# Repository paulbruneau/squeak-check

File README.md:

# Squeak Check!

A bench tester for Midway's Cheap Squeak Deluxe, Sounds Good and Turbo Cheap Squeak arcade sound boards (Spy Hunter, Rampage, Xenophobe, Sarge and more). Power a sound board on the bench, dial a sound 0–F, press PLAY, and hear it on line out, with no game CPU board, harness or cabinet.

By Ethical Paul.

**Website:** the full write-up (how the boards work, pinouts, hook-up diagram, history) is in `index.html`, published with GitHub Pages.

## Files

| Path | What it is |
| --- | --- |
| `fab/SqueakCheck_RevE6_Gerbers.zip` | Gerbers and drill files, Rev E.6 (98 × 80 mm, 2 layers, 1.6 mm) |
| `fab/Schematic_RevE6.pdf` | Schematic, drawn from and checked against the board netlist |
| `fab/KiCad/` | KiCad 8 schematic and PCB, generated from the board data (refill the zone and run DRC after opening) |
| `fab/BOM.csv` | Bill of materials with Mouser part numbers |
| `fab/Harness_Pin_Map.csv` | Every harness hole: connector, pin, label, net, position |
| `fab/README.txt` | Revision history and verification notes |
| `reference/Cheap_Squeak_Deluxe_Schematic.pdf` | Midway's Cheap Squeak Deluxe schematic (A080-91671), for reference |
| `tools/` | Scripts used to edit and check the Gerbers (see `tools/README.md`) |
| `squeak-tap/` | **Squeak Tap**, a companion project: plugs into the CSD's DAC socket and records the sound board's audio as the exact digital values, straight to WAV (see `squeak-tap/README.md`) |
| `fab/fonts/` | Barlow Condensed SemiBold, the silkscreen credit font (SIL OFL) |
| `index.html`, `images/` | The website |

## Building

Fit the hex dial (SW1) with the 0 on its dial toward the top of the board, next to the "0" on the silkscreen. It fits either way round, and the wrong way swaps the sound bits. On Rev E.5 boards the 0 goes toward the bottom edge.

## Ordering boards

Upload the Gerber zip to any 2-layer PCB fab: FR-4, 1.6 mm, 1 oz copper, any mask colour, white silk, HASL or ENIG.

## Squeak Tap

`squeak-tap/` holds a second, separate project: a DAC-socket adapter and a Raspberry Pi Pico capture board, ordered together on one panel and snapped apart. It records the 10-bit values the Cheap Squeak Deluxe writes to its AD7533 DAC and turns them into WAV files, for a bit-exact copy of a sound such as the Spy Hunter theme. Gerbers, schematic, BOM, firmware and the PC tool are all in that folder. Rev A has not been built yet.

## Rights

© 2026 Ethical Paul. All rights reserved. No license is granted yet; ask before reusing the files.

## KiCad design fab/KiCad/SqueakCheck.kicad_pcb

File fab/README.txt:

SQUEAK CHECK! — Midway sound board bench tester — REV E.6
By Ethical Paul
=========================================================

WHAT IT TESTS
-------------
Verified against the original Bally/Midway schematics (Spy Hunter, Rampage/Star
Guards and Sarge manuals). All three boards share the same J1/J2/J3 pinout and the
same command interface (4 sound-select bits + SIRQ strobe, 2 status bits back):

  Cheap Squeak Deluxe  A080-91671 (68000)   Spy Hunter, Turbo Tag (proto)
  Sounds Good          A080-91671-G000 PCB  Rampage, Power Drive, Star Guards,
                       (a later revision of  Xenophobe, Spy Hunter II, Blasted,
                        the same bare board) Intl. Team Laser (proto)
  Turbo Cheap Squeak   (6809)               Sarge, Max RPM, Demolition Derby,
                                            Spy Hunter II (2nd board)

NOT compatible: Super Sound I/O (SSIO), and the Williams System 11 boards in
Arch Rivals / Pigskin / Tri-Sports. Pinball-era Bally boards (Cheap Squeak,
Sounds Deluxe, pinball TCS) use different harnesses and were not checked.

REV E.6: HEX DIAL FITS WITH ITS 0 AT THE TOP.
- On E.5 the SW1 footprint's pin map assumed the Grayhill 94HBB16T went in with
  the 0 on its dial toward the BOTTOM of the board. The switch fits its holes
  either way round, and fitted with 0 at the top (the natural way) it swapped
  SOUND0<->SOUND1 and SOUND2<->SOUND3 (dial 1 sent 2, dial 4 sent 8, etc.).
- E.6 turns the footprint's pin numbers 180 degrees: with the 0 at the top,
  pin 1 is the top-left hole and drives SOUND0. Hole positions are unchanged;
  the four sound tracks are swapped where they meet the resistors:
    SW1 top-left hole     -> S0 (R5/R6)   front copper
    SW1 bottom-right hole -> S1 (R3/R4)   back copper
    SW1 bottom-left hole  -> S2 (R9/R10)   front copper
    SW1 top-right hole    -> S3 (R7/R8)   back copper
- Silkscreen: a "0" replaces the top dial tick and an "8" the bottom one, so
  the switch's printed 0 lines up with the silk 0. REV E.5 -> REV E.6.
- Silkscreen text: every label is now at least 1.1 mm tall (capital height)
  with strokes of about 0.2 mm; the smallest used to be 0.72 mm. Grown in
  place: the LED legend, LINE LEVEL note, power-tag pills, F1/F2/5V/12V,
  resistor values, column headings, TRIGGER, 1uF, AWG notes, LOUDER/VOLUME,
  PICK A SOUND, INSERT POWER / KK-396, and the size and mounting notes.
  "5V 1A · 12V 0.5A" is now two lines ("5V 1A" / "12V 0.5A") to clear the
  RCA jack outline. Nothing moved onto pads; copper and drills unchanged.
- Header under the title is now two stacks. Left: "By Ethical Paul" (1.75 mm)
  over "paul@ethicalpaul.com" (1.47 mm), both Barlow Condensed SemiBold. Right, at 1.3 mm: CHEAP SQUEAK DELUXE / SOUNDS GOOD
  / TURBO CHEAP SQUEAK (replaces the one-line "... · BENCH TESTER" subtitle).
- REV E.6 / board size / mounting block scaled up 1.6x (REV 2.2 mm, notes
  1.8 mm) and centred in the open area between the SOUND2 row and J2.
- Three small ground-pour keep-outs on the back (around 29.8,51.8 / 32.3,47.4 /
  30.9,30.1 in Gerber coordinates) stop the rerouted tracks from leaving an
  unconnected pour island and two thin necks.
- Schematic unchanged electrically (dial 1-2-4-8 -> SOUND0-3); the KiCad
  symbol now lists SW1's pins in footprint order (1, CL, 4, 8, CR, 2).
- E.5 BOARDS: fit SW1 with its 0 toward the BOTTOM edge to get the right bits.
- Resistor references renumbered to the usual R1-R13 (silkscreen unchanged;
  it prints values, not references). Old -> new: RSIRQ R1, RIRQ R2, RS1 R3,
  RPD1 R4, RS0 R5, RPD0 R6, RS3 R7, RPD3 R8, RS2 R9, RPD2 R10, RL1 R11,
  RL2 R12, RRST R13. The notes below use the new names.
Every other hole, part, net and label is unchanged from E.5.

REV E.5: POWER PROTECTION AND INDICATORS (review feedback).
- F1 (Bourns MF-R135, 1.35 A hold) on +5 V and F2 (MF-R050, 0.5 A hold) on +12 V:
  resettable fuses right after the power header, so a shorted sound board
  can't cook the tester's traces or connector.
- D1/D2 green LEDs on +5 V and +12 V, AFTER the fuses (1k / 3.3k, ~3 mA): a dark
  LED means no supply or a tripped fuse.
- Suggested supply printed on the board: 5 V 1 A, 12 V 0.5 A (estimated from
  the sound board's chips; measure your own board).
- Mounting note on the silk: M3 or #4-40, pan head no bigger than 5.6 mm.
- LED self-test legend moved into the how-to panel to make room.
Harness holes, pin order, names and every sound-board signal are unchanged.

REV E.4: BOARD NARROWED 108 -> 98 MM. J1 stays on the left edge; the resistor
block tucked in against the J1 labels and everything else slid left (J2, J3, pot,
RCA jacks and power header move as groups, with pitches, hole sizes, pin order and
labels all unchanged). +12V now runs between the SOUND2 trace (SOUND3 from
E.6 on) and the RESET button on the back. Netlist identical to E.3.

REV E.3: VOLUME POT ON THE BOARD. The J5 A/W/B wire pads are gone; RV1 (Bourns
PTV09A-4020U-B102, 1k linear, 9 mm, vertical 20 mm knurled shaft
you turn by hand - no knob needed) sits in the
bottom-right corner, wired pin 1 = VOL_END_B (J3-12), pin 2 = VOL_WIPER (J3-1),
pin 3 = VOL_END_A (J3-10) so turning it CLOCKWISE = LOUDER (the MC3340 attenuates
more as the wiper voltage rises). Its two side tabs are soldered to ground for
strength. Every other net, hole and label is unchanged from E.2. Part numbers in
BOM.csv are Mouser numbers.

REV E.2 (layout): PLAY button and its debounce cap moved right beside the hex
dial; "By Ethical Paul" added under the title. No circuit change from E.1.

REV E.1 CHANGES (from Rev E / Rev D5)
------------------------------------
1. RESET POLARITY FIXED. J2-9/10 is active-LOW on all three boards (e.g. CSD:
   100k pull-up -> 40106 -> 74LS04 -> diodes pull the 68000 RST/HALT low). Rev D5
   held RESET low through 10k, which would keep the board in reset permanently.
   Now: R13 (10k) pulls RESET up to +5V; the RESET button pulls it to GND.
2. SIRQ polarity hardwired "fire low"; JP1 removed. All three boards idle SIRQ
   high (100k on-board pull-up) and the same game hardware drives them with the
   same signal (Spy Hunter II feeds a Sounds Good and a TCS from the same control
   bits). R2 (10k) pulls SIRQ up to +5V; PLAY pulls it to GND.
3. PLAY debounce: C1 1 uF across the button (~10 ms with R2).
4. E-GND (J2-7) tied to GND. Sounds Good grounds it on-board; CSD/TCS use it as
   the return for their input filter capacitors.
Harness hole sizes, pin order, duplicate pins and all silk names are unchanged.

USING IT
--------
Power-up: the sound board's green LED flashes once per passed self-test:
  1-4 = ROMs (U7, U8, U17, U18), 5 = RAM (U6, U16), 6 = PIA (U9).
  Six flashes = pass. Where it stops = the failed step. (Star Guards manual.)

Red TEST button ON the sound board: wired to the 68000's interrupt lines
(pulls IPL0-2 -> level 7). What it does is decided by that game's ROMs. On the
sister pinball boards it plays one fixed test sound (a "bong" or an explosion)
or just reboots the board; it is not a cycle through all sounds.

Sound numbers: the connector carries 4 bits per strobe; one dial+PLAY press
sends the number on the dial. The command list lives in each game's sound ROMs
and is not documented in MAME. Spy Hunter CSD (only the two low bits matter):
1 = full Peter Gunn theme, 2 = short intro, 3 = the "player died" ending (send
it while the theme is playing). Other games' ROMs may expect a sequence of
presses.

Start with the VOLUME knob turned down (fully counter-clockwise). Line-level mono audio
appears on both RCA jacks; feed an amplifier or powered speaker.

VERIFICATION (Rev E.6)
---------------------
Gerbers re-read with an independent parser and rasterised at 0.04 mm:
- Netlist: every one of the 135 holes' copper checked against the intended
  net (23 nets): 0 shorts, 0 opens, 0 unconnected copper islands.
- Clearance between different nets: 0.50 mm minimum on top, 0.40 mm on the
  back (rule 0.30 mm). Same as E.5; the rerouted tracks have 0.68 mm or more.
- Thin copper: the new keep-outs leave four tiny pointed tips of ground pour
  (under 0.3 mm long), the same kind of feature E.5 already had at its
  thermal spokes and corners. Fabs handle these.
- Drills: 98 plated + 37 non-plated, all on their pads; files unchanged from E.5.
- Silkscreen: none on exposed pads; all text at least 1.1 mm tall and
  0.2 mm or more from other silk (the power tags keep their E.5 spacing).
- KiCad PCB tracks and pads redrawn and compared with the Gerber copper:
  identical on top, and every KiCad track present on the back.
(No KiCad/Altium DRC was run here. Preview the zip in your fab's Gerber viewer
before ordering.)

ORDERING
--------
2 layers, FR-4, 1.6 mm, 1 oz, any mask colour, white silk, ENIG or HASL.
98 x 80 mm. Upload SqueakCheck_RevE6_Gerbers.zip as it is.

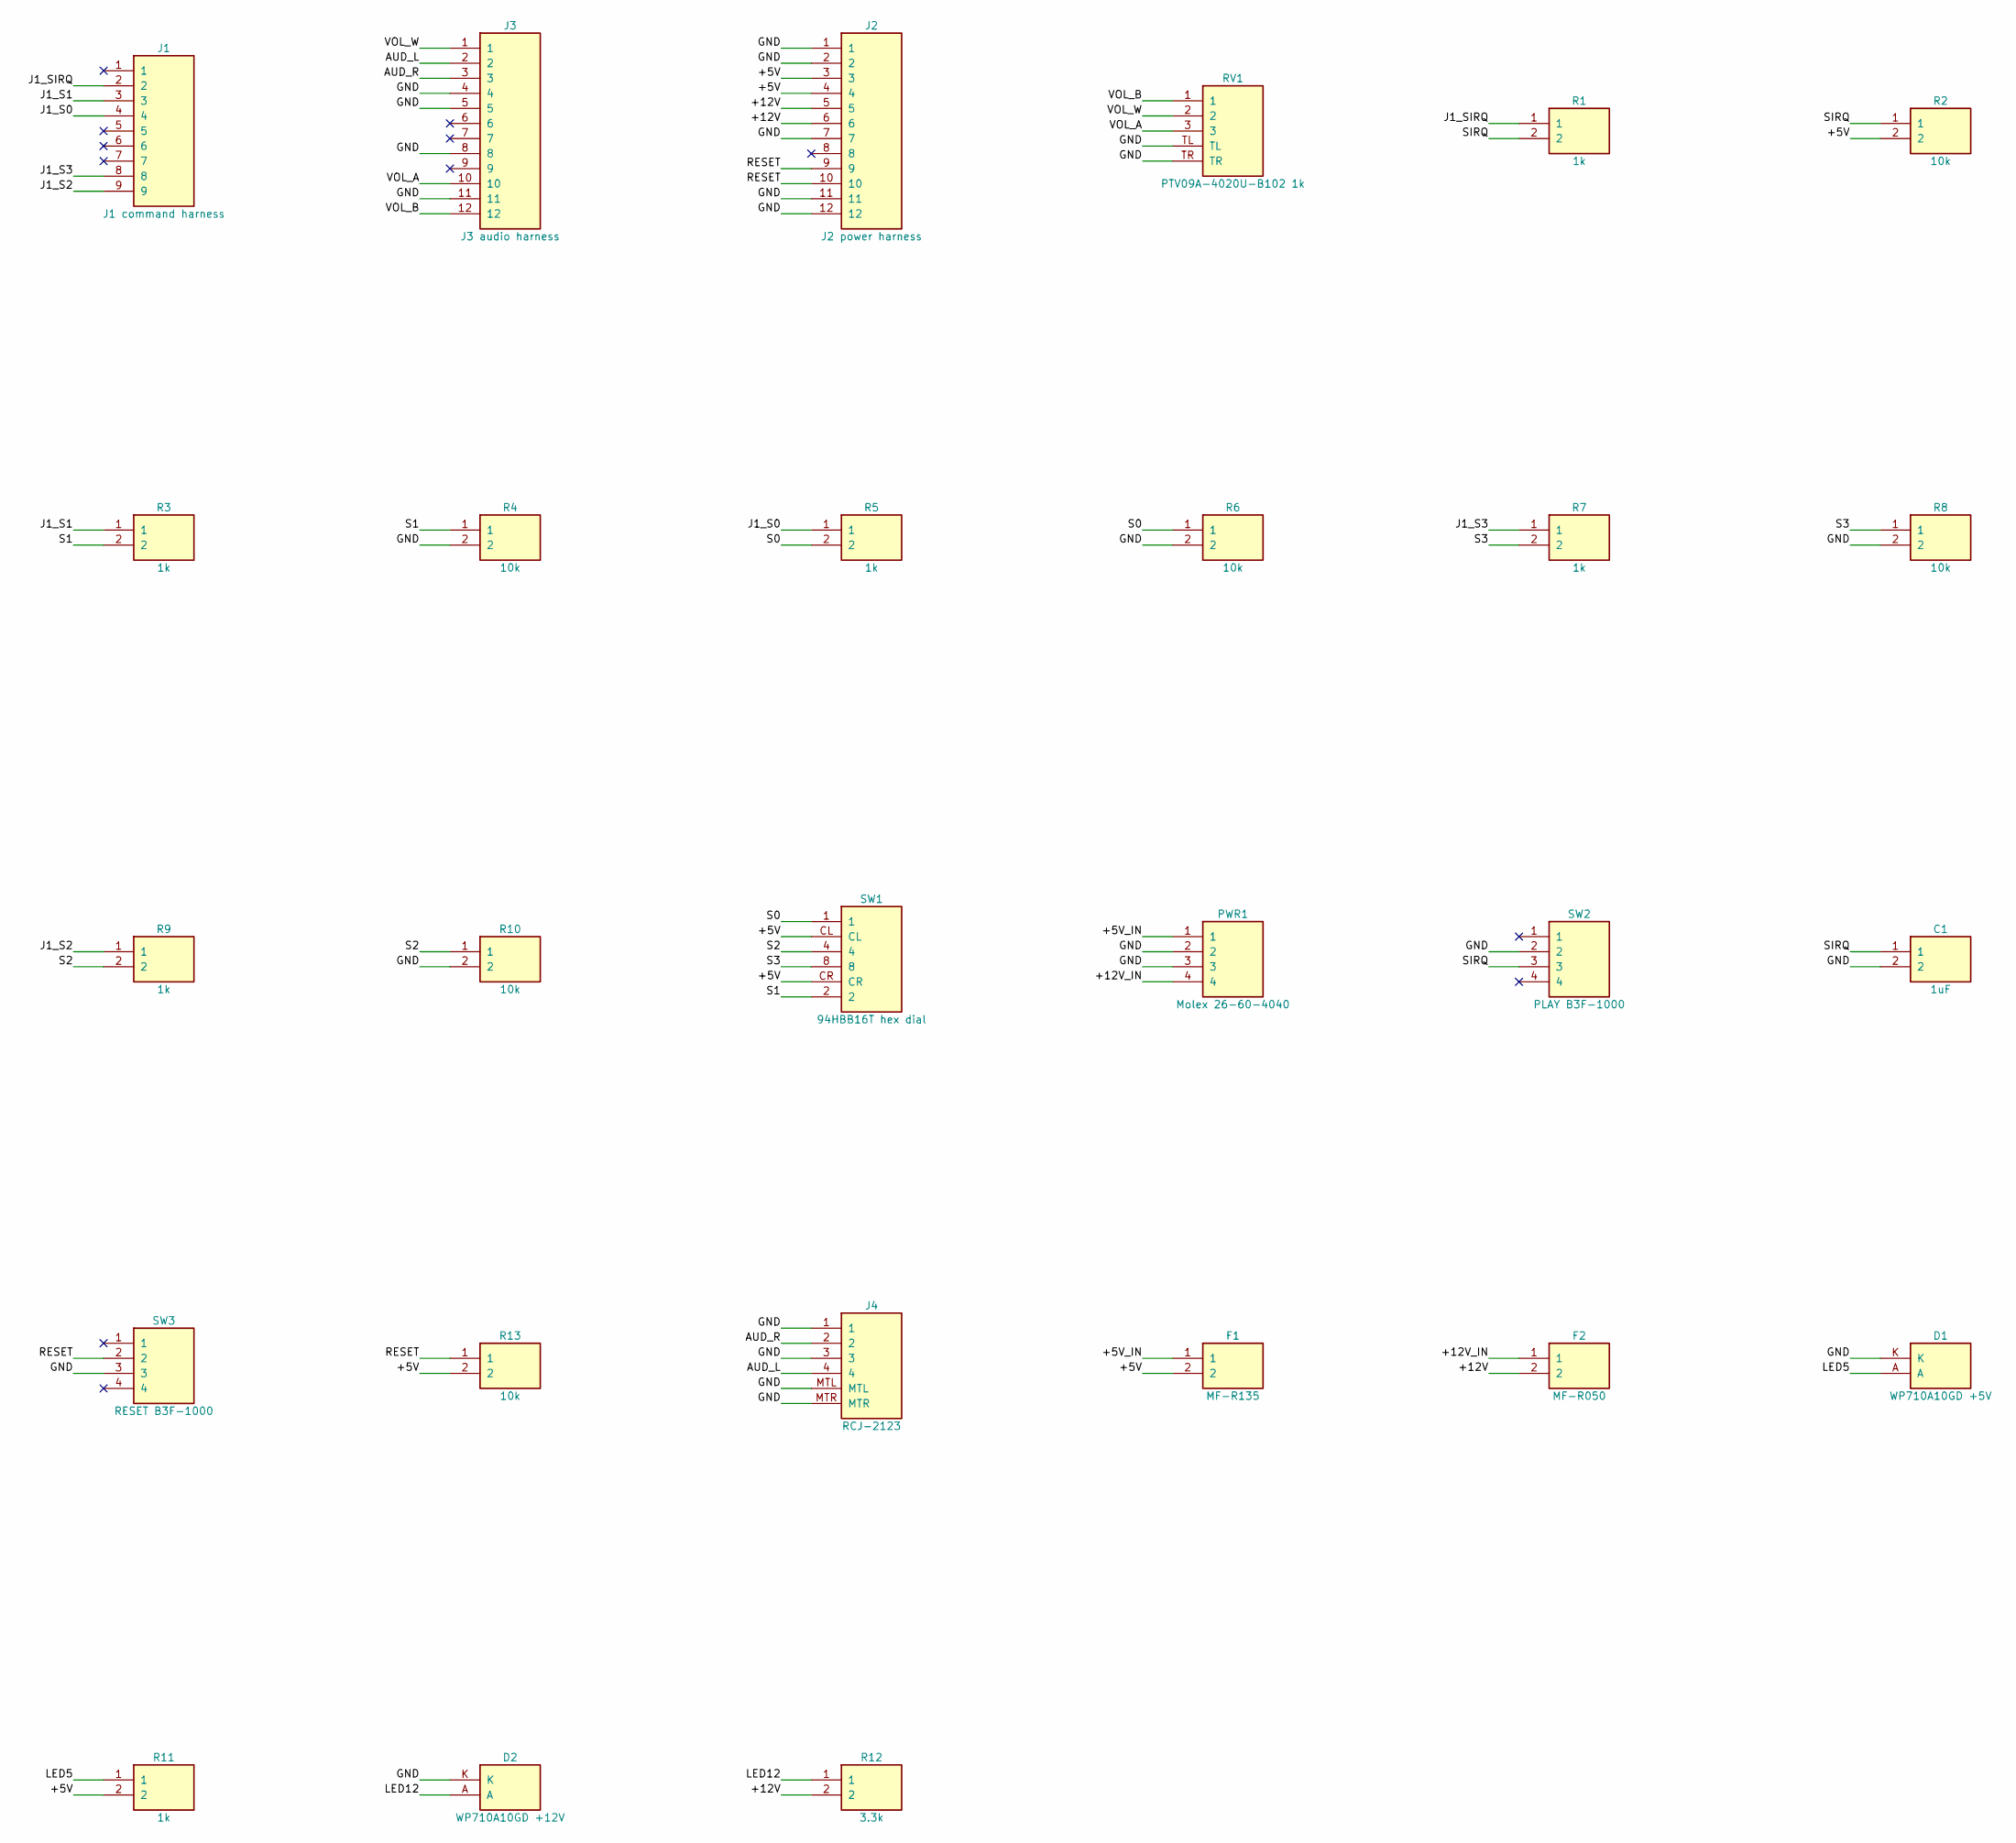
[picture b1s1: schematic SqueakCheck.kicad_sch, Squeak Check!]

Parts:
C1: 1uF; C1
D1: WP710A10GD +5V; D1
D2: WP710A10GD +12V; D2
F1: MF-R135; F1
F2: MF-R050; F2
J1: J1 command harness; J1
J2: J2 power harness; J2
J3: J3 audio harness; J3
J4: RCJ-2123; J4
PWR1: Molex 26-60-4040; PWR1
R1: 1k; R1
R2: 10k; R2
R3: 1k; R3
R4: 10k; R4
R5: 1k; R5
R6: 10k; R6
R7: 1k; R7
R8: 10k; R8
R9: 1k; R9
R10: 10k; R10
R11: 1k; R11
R12: 3.3k; R12
R13: 10k; R13
RV1: PTV09A-4020U-B102 1k; RV1
SW1: 94HBB16T hex dial; SW1
SW2: PLAY B3F-1000; SW2
SW3: RESET B3F-1000; SW3

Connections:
+5V: F1.2, J2.3, J2.4, R2.2, R11.2, R13.2, SW1.CL, SW1.CR
+5V_IN: F1.1, PWR1.1
+12V: F2.2, J2.5, J2.6, R12.2
+12V_IN: F2.1, PWR1.4
AUD_L: J3.2, J4.4
AUD_R: J3.3, J4.2
GND: C1.2, D1.K, D2.K, J2.1, J2.2, J2.7, J2.11, J2.12, J3.4, J3.5, J3.8, J3.11, J4.1, J4.3, J4.MTL, J4.MTR, PWR1.2, PWR1.3, R4.2, R6.2, R8.2, R10.2, RV1.TL, RV1.TR, SW2.2, SW3.3
J1_S0: J1.4, R5.1
J1_S1: J1.3, R3.1
J1_S2: J1.9, R9.1
J1_S3: J1.8, R7.1
J1_SIRQ: J1.2, R1.1
LED5: D1.A, R11.1
LED12: D2.A, R12.1
RESET: J2.9, J2.10, R13.1, SW3.2
S0: R5.2, R6.1, SW1.1
S1: R3.2, R4.1, SW1.2
S2: R9.2, R10.1, SW1.4
S3: R7.2, R8.1, SW1.8
SIRQ: C1.1, R1.2, R2.1, SW2.3
VOL_A: J3.10, RV1.3
VOL_B: J3.12, RV1.1
VOL_W: J3.1, RV1.2

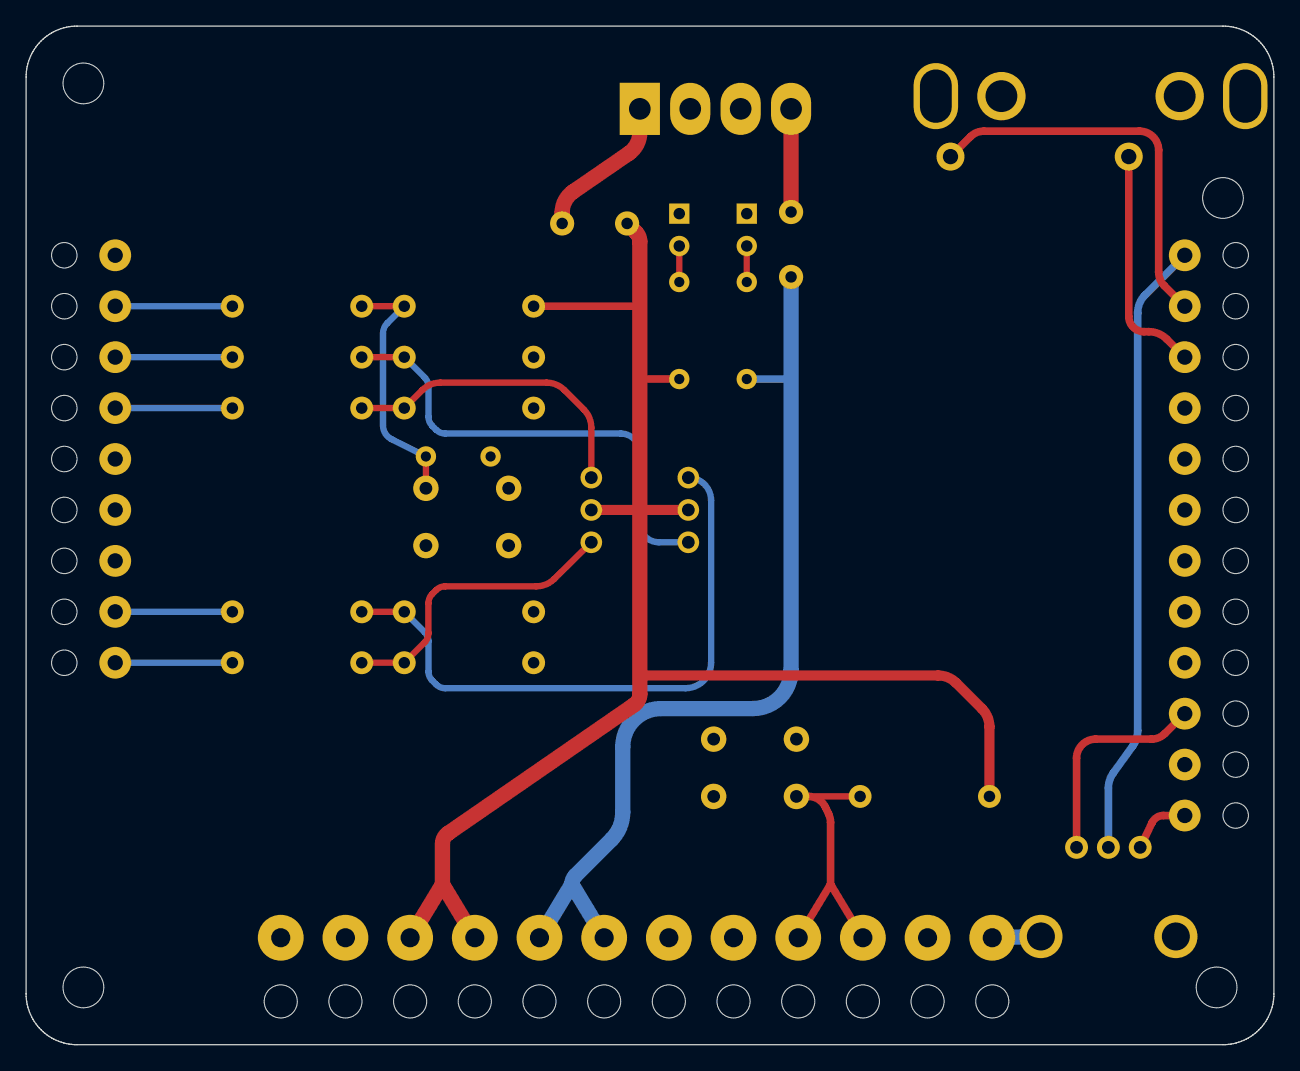
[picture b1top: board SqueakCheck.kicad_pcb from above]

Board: 2 copper layers, 98.0 x 80.0 mm, 64 parts (0 on the bottom side), 23 nets.

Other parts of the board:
H1, H2, H3, H4, H5, H6, H7, H8, H9, H10, H11, H12, H13, H14, H15, H16, H17, H18, H19, H20, H21: hole 2; NPTH_2mm
H22, H23, H24, H25, H26, H27, H28, H29, H30, H31, H32, H33: hole 2.6; NPTH_2.6mm
H34, H35, H36, H37: hole 3.2; NPTH_3.2mm

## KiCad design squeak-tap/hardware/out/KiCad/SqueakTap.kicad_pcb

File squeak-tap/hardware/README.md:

# Squeak Tap Rev A: board files

Two boards on one 91 × 60 mm panel, separated by a 2 mm routed gap and held by three mouse-bite tabs laid out to JLCPCB's mouse-bite guide. Order the panel, snap the tabs, sand the nubs. By Ethical Paul.

| Board | Size | What it does |
| --- | --- | --- |
| 1, DAC adapter | 34 × 37 mm | Plugs into the CSD's DAC socket (U10). The original AD7533 sits in X1, 12.7 mm to the side, and still drives the CSD's audio. The 10 data bits and ground go to J2. |
| 2, capture board | 55 × 60 mm | Two 74LVC245 buffers (5 V in, 3.3 V out), a 100 k pull-down network and a Pico 2 that samples the bits at 960 kHz and streams them over USB. MARK button on GP12. |

## Files

| Path | What it is |
| --- | --- |
| `out/SqueakTap_RevA_Gerbers.zip` | Gerbers + Excellon (PTH and NPTH), the file to upload |
| `out/Schematic_RevA.pdf` | Schematic, two A3 sheets, drawn from the board netlist |
| `out/BOM.csv` | Bill of materials |
| `out/Ribbon_Pin_Map.csv` | Every ribbon pin: signal, CSD source, buffer input, Pico GPIO |
| `out/KiCad/SqueakTap.kicad_pcb` | KiCad 8 PCB: copper, drills, outline, nets, GND zone (refill it after opening; silkscreen lives in the Gerbers) |
| `make_panel.py` | Generates the Gerbers, drills and KiCad file |
| `make_docs.py` | Generates the schematic, BOM and pin map from the KiCad netlist |
| `tools/` | Squeak Check's Gerber reader, DRC and renderer, set for this panel |

Regenerate with `python3 make_panel.py && python3 make_docs.py`, then check with `python3 tools/drc.py out/Gerbers out/KiCad/SqueakTap.kicad_pcb 40`.

## Ordering

Upload `SqueakTap_RevA_Gerbers.zip` to any 2-layer fab: FR-4, 1.6 mm, 1 oz, HASL or ENIG, any mask colour, white silk.

- Tell the fab the file is a **panel you made yourself, with 2 different designs separated by a perforated (mouse-bite) line**: on the order page after uploading, set "Different Design" to 2 and "Delivery Format" to "Panel by Customer" (JLCPCB's names; other fabs have equivalents). Some fabs add a small charge for 2 designs.
- Layout follows JLCPCB's mouse-bite guide: a 2.0 mm routed gap (they recommend 1.6–2 mm), three 6 mm tabs, and on each tab a row of six non-plated 0.6 mm holes along each board's edge, 0.96 mm apart (0.36 mm webs; they recommend 0.35–0.4 mm and 5–8 holes per set). Hole centres sit 0.15 mm inside each board so the snapped nubs stay within the outline.
- To separate: hold Board 2 flat and bend Board 1 down; the three tabs break along the holes. Sand the nubs flush. Copper stays at least 1 mm back from the gap on both boards.

## Assembly notes

- **Board 1:** fit X1 (socket) on the top. Fit the two P1 pin strips from the **bottom**, thin ends down, and solder them from the top. Pin 1 is the square pad on both, marked with a triangle. The AD7533 goes into X1 with its notch matching the silk notch.
- **Board 2:** fit the Pico on female headers, not flat: C1 and C2 sit under its edge. RN1's pin 1 (common, dot on the part) goes to the square pad at the top. Box headers J1/J2 go with their key slots toward the silk key marks.
- **Ribbon:** a straight 16-way IDC cable, both sockets crimped the same way round, so pin 1 meets pin 1.
- **Fitting to the CSD:** power off, lift the AD7533 out of U10, plug Board 1's P1 in with pin 1 matching the CSD's U10 pin 1, then put the AD7533 into X1. Fitted backwards, P1 would put +12 V on a data line.

## Design checks (Rev A)

- Netlist: every pad's net matches the copper (F and B joined at plated holes): no shorts, no opens, no copper islands.
- Clearance between nets: 0.31 mm minimum on top, 0.28 mm on the bottom. Signal traces 0.25 mm, 3V3 0.3 mm, Board 1 ground 0.5 mm.
- Silkscreen clear of every mask opening on both sides.
- AD7533 pinout on Board 1 checked against the A080-91671 schematic: BIT1–BIT8 from PIA PA7–PA0, BIT9 from PB7, BIT10 from PB6, VDD +12 V on pin 14 (passed through only).
- Ribbon bit order is D5–D9 then D0–D4 so neither board's traces cross; the firmware rotates it back, and that rotation is checked against the board netlist.
- Not yet built: the panel hasn't been fabricated or fitted to a CSD.

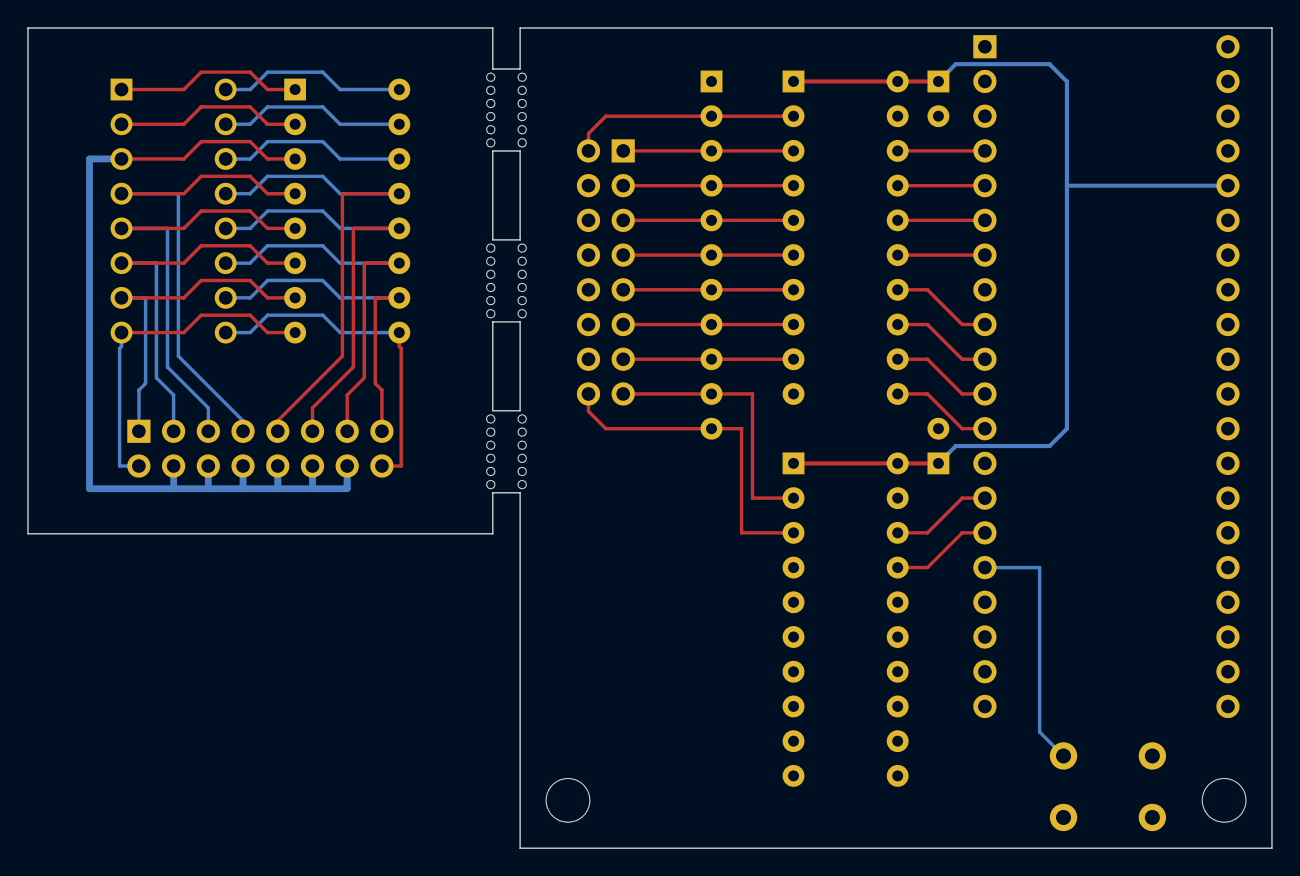
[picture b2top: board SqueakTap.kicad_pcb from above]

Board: 2 copper layers, 91.0 x 60.0 mm, 16 parts (0 on the bottom side), 39 nets.

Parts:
A1: Raspberry Pi Pico 2; A1
C1: 100nF; C1
C2: 100nF; C2
H1: M3; H1
H2: M3; H2
J1: Ribbon from DAC adapter; J1
J2: Ribbon to capture board; J2
P1: CSD U10 plug (pin strips); P1
RN1: 100k bussed x10; RN1
SW1: MARK; SW1
TAB1: mouse bites; TAB1
TAB2: mouse bites; TAB2
TAB3: mouse bites; TAB3
U1: 74LVC245; U1
U2: 74LVC245; U2
X1: AD7533 socket; X1

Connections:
+3V3: A1.36, C1.1, C2.1, U1.1, U1.20, U2.1, U2.20
ADP_12V: P1.14, X1.14
ADP_D0: J2.9, P1.13, X1.13
ADP_D1: J2.11, P1.12, X1.12
ADP_D2: J2.13, P1.11, X1.11
ADP_D3: J2.15, P1.10, X1.10
ADP_D4: J2.16, P1.9, X1.9
ADP_D5: J2.2, P1.8, X1.8
ADP_D6: J2.1, P1.7, X1.7
ADP_D7: J2.3, P1.6, X1.6
ADP_D8: J2.5, P1.5, X1.5
ADP_D9: J2.7, P1.4, X1.4
ADP_GND: J2.4, J2.6, J2.8, J2.10, J2.12, J2.14, P1.3, X1.3
ADP_OUT2: P1.2, X1.2
ADP_REF: P1.1, X1.1
ADP_RFB: P1.16, X1.16
ADP_VOUT: P1.15, X1.15
D0: J1.9, RN1.7, U1.7
D1: J1.11, RN1.8, U1.8
D2: J1.13, RN1.9, U1.9
D3: J1.15, RN1.10, U2.2
D4: J1.16, RN1.11, U2.3
D5: J1.2, RN1.2, U1.2
D6: J1.1, RN1.3, U1.3
D7: J1.3, RN1.4, U1.4
D8: J1.5, RN1.5, U1.5
D9: J1.7, RN1.6, U1.6
GND: A1.3, A1.8, A1.13, A1.18, A1.23, A1.28, A1.38, C1.2, C2.2, J1.4, J1.6, J1.8, J1.10, J1.12, J1.14, RN1.1, SW1.4, U1.10, U1.19, U2.4, U2.5, U2.6, U2.7, U2.8, U2.9, U2.10, U2.19
GP2: A1.4, U1.18
GP3: A1.5, U1.17
GP4: A1.6, U1.16
GP5: A1.7, U1.15
GP6: A1.9, U1.14
GP7: A1.10, U1.13
GP8: A1.11, U1.12
GP9: A1.12, U1.11
GP10: A1.14, U2.18
GP11: A1.15, U2.17
MARK: A1.16, SW1.1
